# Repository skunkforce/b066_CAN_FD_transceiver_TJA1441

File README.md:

# edgy_board number b066
This design is part of the [edgy board project](https://github.com/skunkforce/edgy_boards).

# getting started
This repository uses submodules. After cloning use the command 

```$ git submodule update --init --recursive```

to pull the submodules before opening the project with kicad. 

# Tests
Tests can be found in [TESTS.md](TESTS.md)

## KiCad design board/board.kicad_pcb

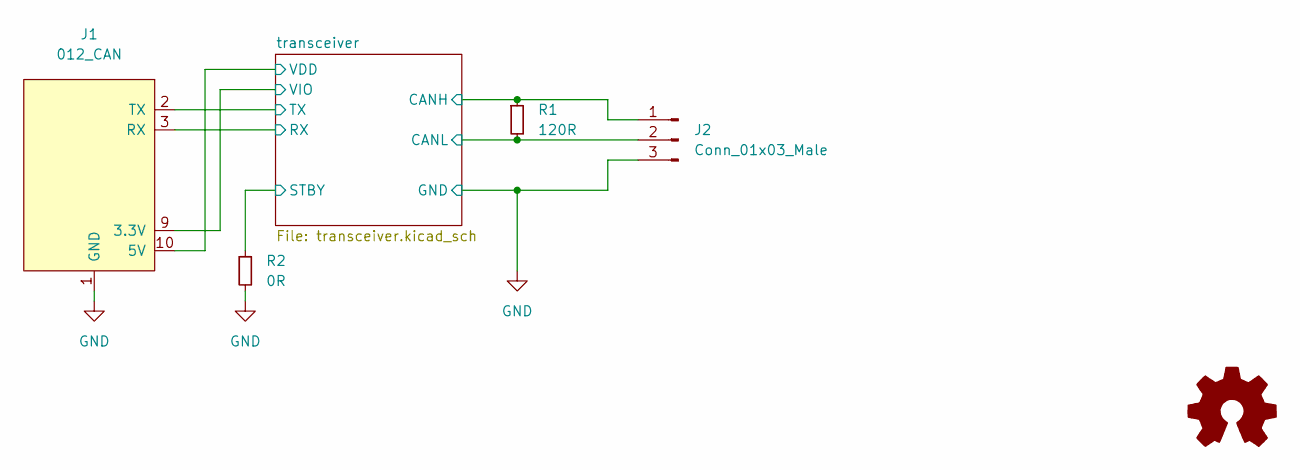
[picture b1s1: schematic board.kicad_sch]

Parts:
J1: 012_CAN; on_edge_2x05_device
J2: Conn_01x03_Male; PinHeader_1x03_P2.54mm_Vertical
LOGO1: Logo_Open_Hardware_Small; OSHW-Symbol_6.7x6mm_SilkScreen
R1: 120R; R_0805_2012Metric; lcsc C17437
R2: 0R; R_0603_1608Metric; lcsc C21189

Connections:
/transceiver/CANH: J2.1, R1.1; also elsewhere on the board
/transceiver/CANL: J2.2, R1.2; also elsewhere on the board
/transceiver/RX: J1.3 (RX); also elsewhere on the board
/transceiver/STBY: R2.1; also elsewhere on the board
/transceiver/TX: J1.2 (TX); also elsewhere on the board
/transceiver/VDD: J1.10 (5V); also elsewhere on the board
/transceiver/VIO: J1.9 (3.3V); also elsewhere on the board
GND: J1.1 (GND), J2.3, R2.2; also elsewhere on the board

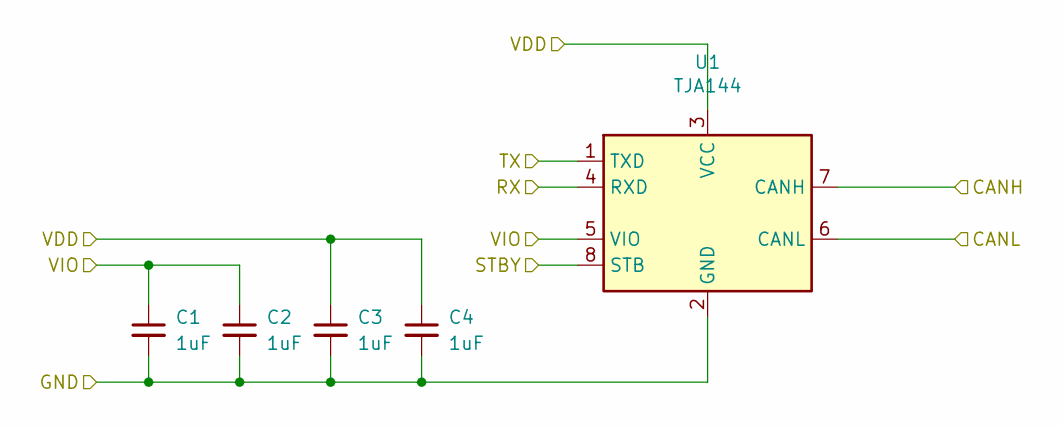
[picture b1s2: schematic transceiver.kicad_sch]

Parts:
C1, C2, C3, C4: 1uF; C_0603_1608Metric; lcsc C15849
U1: TJA144; SOIC-8_3.9x4.9mm_P1.27mm; MPN TJA1441AT/0Z; lcsc C961486

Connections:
/transceiver/CANH: U1.7 (CANH); also elsewhere on the board
/transceiver/CANL: U1.6 (CANL); also elsewhere on the board
/transceiver/RX: U1.4 (RXD); also elsewhere on the board
/transceiver/STBY: U1.8 (STB); also elsewhere on the board
/transceiver/TX: U1.1 (TXD); also elsewhere on the board
/transceiver/VDD: C3.1, C4.1, U1.3 (VCC); also elsewhere on the board
/transceiver/VIO: C1.1, C2.1, U1.5 (VIO); also elsewhere on the board
GND: C1.2, C2.2, C3.2, C4.2, U1.2 (GND); also elsewhere on the board

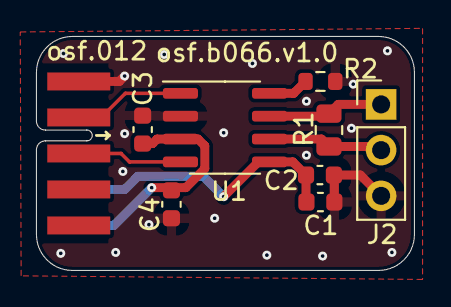
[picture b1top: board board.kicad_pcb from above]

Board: 2 copper layers, 21.0 x 13.0 mm, 10 parts (1 on the bottom side), 8 nets.

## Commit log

2023-05-02 initial
2023-05-03 added render
2024-06-29 changed transceiver chip to be more availible TJA1044GT version
